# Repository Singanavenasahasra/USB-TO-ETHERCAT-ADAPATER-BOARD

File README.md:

# USB-to-EtherCAT Adapter Board

A compact hardware platform developed for interfacing USB systems with EtherCAT-based networks. The board was designed in KiCad with emphasis on clean circuit organization, efficient PCB routing, and practical hardware integration.

## Tools
- KiCad
- PCB Design & Layout

## Output
- Schematic
- PCB Layout
- Gerber Files
- Drill Files
- BOM

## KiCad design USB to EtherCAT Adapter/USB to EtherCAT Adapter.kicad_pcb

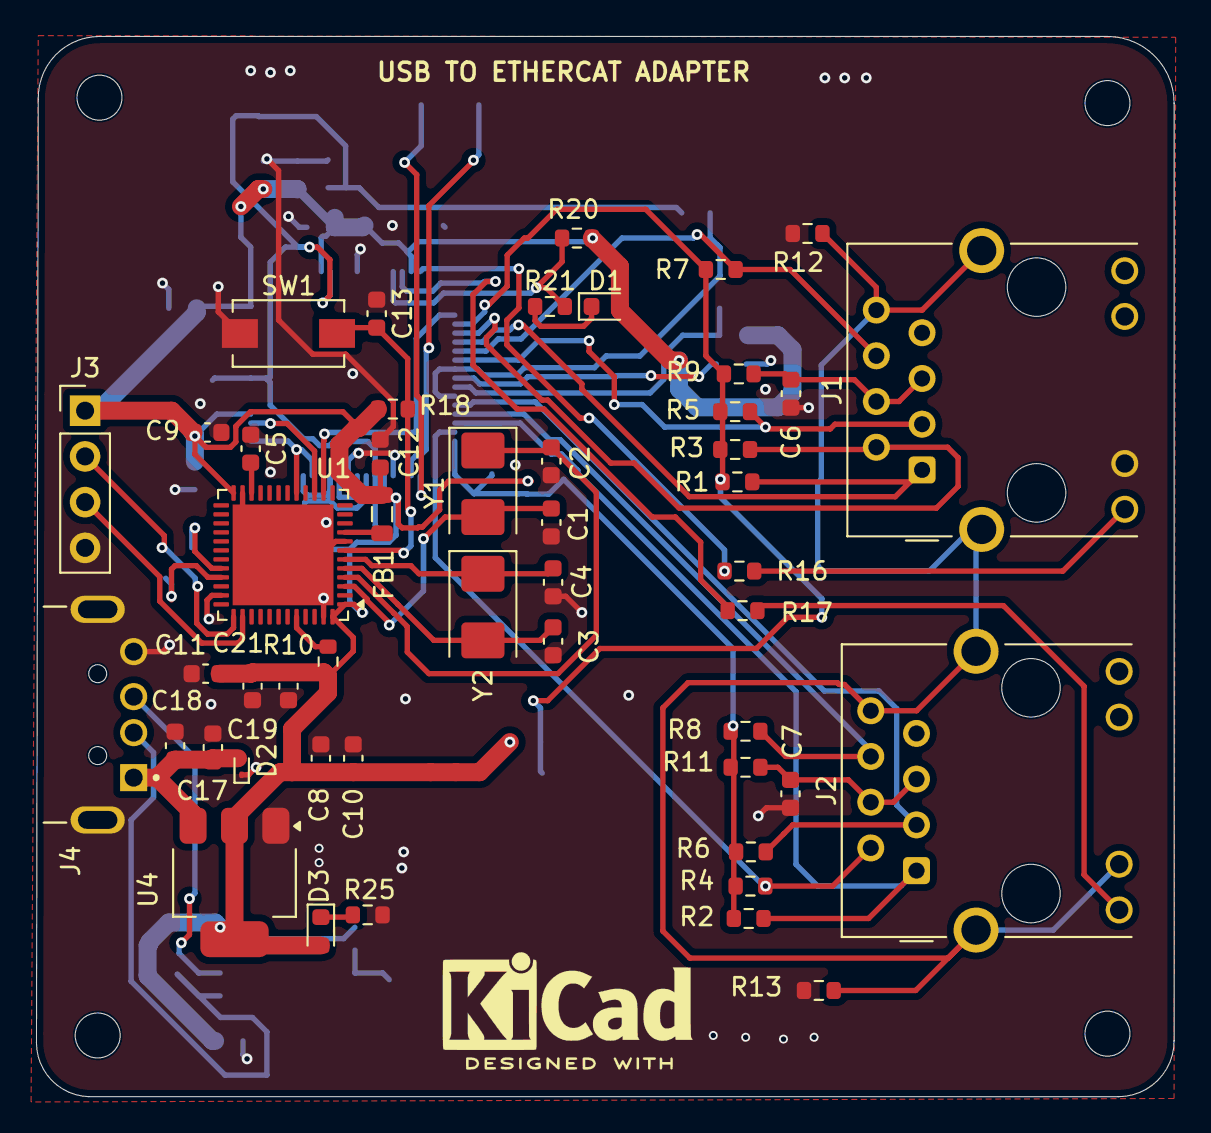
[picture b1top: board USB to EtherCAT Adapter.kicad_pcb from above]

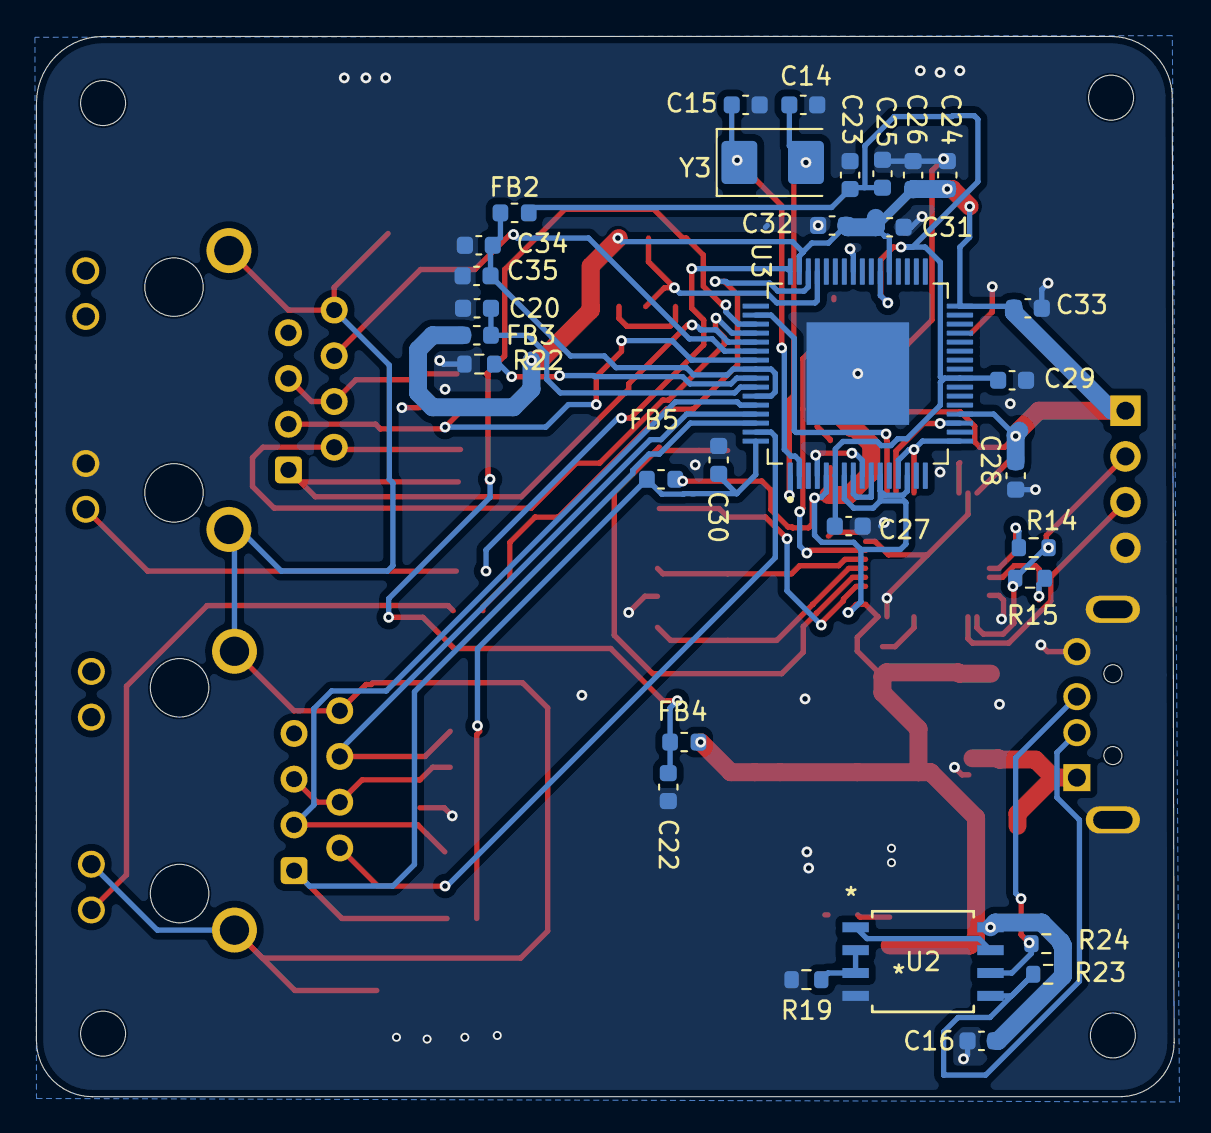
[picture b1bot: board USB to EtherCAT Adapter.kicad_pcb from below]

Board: 2 copper layers, 63.2 x 58.9 mm, 84 parts (31 on the bottom side), 49 nets.

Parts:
C1, C2, C3, C4, C14, C15: 12pf; C_0603_1608Metric
C5: 2.2uF; C_0603_1608Metric
C6, C7: 0.022uf; C_0603_1608Metric
C8, C9, C10, C11, C12, C13, C18, C19, C20, C22, C23, C24, C25, C26, C27, C28, C29, C30, C31, C32, C33, C34, C35: 0.1uf; C_0603_1608Metric
C16, C17, C21: 10uf; C_0603_1608Metric
D1, D3: LED; LED_0603_1608Metric
D2: ESD9B5.0ST5G; D_SOD-923
FB1: FerriteBead; L_0805_2012Metric
FB2: FerriteBead; L_0603_1608Metric
FB3, FB4, FB5: BLM18EG221SN1D; L_0603_1608Metric
H1, H2, H3, H4: MountingHole; MountingHole_2.5mm
J1, J2: RJ45_Hanrun_HR911105A_Horizontal
J3: Conn_01x04; PinHeader_1x04_P2.54mm_Vertical
J4: UP2-AH-1-TH; CUI_UP2-AH-1-TH
R1, R2, R3, R4, R5, R6, R7, R8: 49.9R; R_0603_1608Metric
R9, R11, R12, R13: 0R; R_0603_1608Metric
R10, R18: 10K; R_0603_1608Metric
R14, R15: 10R; R_0603_1608Metric
R16, R17, R20, R21, R25: 220R; R_0603_1608Metric
R19, R23, R24: 4.7K; R_0603_1608Metric
R22: 12.1K; R_0603_1608Metric
SW1: SW_Push; SW_SPST_EVQPE1
U1: STM32F411CEUx; QFN-48-1EP_7x7mm_P0.5mm_EP5.6x5.6mm
U2: 24FC512T-I/SM; SOIJ8-M_MC_MCH
U3: LAN9252_PT; QFP50P1200X1200X120-65N
U4: AMS1117-3.3; SOT-223-3_TabPin2
Y1, Y2, Y3: Crystal; Crystal_SMD_5032-2Pin_5.0x3.2mm

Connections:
+3V3: C8.1, C9.1, C10.1, C11.1, C12.1, C16.2, C19.2, C21.2, C24.2, C26.2, C28.2, C31.2, C32.2, C33.2, D1.2 (A), D3.2 (A), FB1.2, FB3.1, FB4.2, FB5.2, J3.1, R10.1, R18.1, R20.1, R23.2, R24.2, U1.1 (VBAT), U1.24 (VDD), U1.48 (VDD), U2.8 (VCC), U3.5 (VDD33), U3.7 (REG_EN), U3.11 (~RST), U3.14 (VDDIO), U3.20 (VDDIO), U3.32 (VDDIO), U3.37 (VDDIO), U3.47 (VDDIO), U4.2 (VO)
+5V: C17.2, C18.2, D2.2 (A2), J4.1 (VCC), U4.3 (VI)
GND: C1.1, C2.1, C3.1, C4.1, C5.1, C6.1, C7.1, C8.2, C9.2, C10.2, C11.2, C12.2, C13.1, C14.1, C15.1, C16.1, C17.1, C18.1, C19.1, C20.1, C21.1, C22.1, C23.1, C24.1, C25.1, C26.1, C27.1, C28.1, C29.1, C30.1, C31.1, C32.1, C33.1, C34.1, C35.1, D2.1 (A1), J1.10, J3.4, J4.4 (GND), J4.SH1 (SHIELD), J4.SH2 (SHIELD_1), R12.1, R13.1, R19.1, R22.1, R25.2, SW1.1, U1.8 (VSSA), U1.23 (VSS), U1.35 (VSS), U1.47 (VSS), U1.49 (VSS), U2.4 (VSS), U3.4 (OSCVSS), U3.9 (FXSDA/FXLOSA/~FXSDENA), U3.41 (TESTMODE), U3.65 (VSS), U4.1 (GND)
GNDA: J1.8, J1.SH, J2.8, J2.10, J2.SH, R12.2, R13.2
GPIO0: R16.2, U3.48 (LINKACTLED0/TDO/~CHIP_MODE0)
GPIO1: R17.2, U3.46 (LINKACTLED1/TDI/~CHIP_MODE1)
GPIO2: R20.2, R21.2, U3.45 (RUNLED/~E2PSIZE)
unnamed: D1.1 (K), R21.1
unnamed: D3.1 (K), R25.1
unnamed: J1.9, R16.1
unnamed: C6.2, J1.4 (TCT), J1.5 (RCT), R9.2
unnamed: J2.9, R17.1
unnamed: C7.2, J2.4 (TCT), J2.5 (RCT), R11.2
unnamed: R10.2, U1.44 (BOOT0)
unnamed: R14.1, U1.32 (PA11)
unnamed: R15.1, U1.33 (PA12)
unnamed: C1.2, U1.3 (PC14), Y1.2
unnamed: C2.2, U1.4 (PC15), Y1.1
unnamed: C3.2, U1.5 (PH0), Y2.2
unnamed: C4.2, U1.6 (PH1), Y2.1
unnamed: C5.2, U1.22 (VCAP1)
unnamed: FB1.1, U1.9 (VDDA)
unnamed: U2.1 (A0), U2.7 (WP)
unnamed: R19.2, U2.2 (A1), U2.3 (A2)
unnamed: U3.8 (~FXLOSEN), U3.10 (FXSDB/FXLOSB/~FXSDENB)
unnamed: C14.2, U3.1 (OSCI), Y3.2
unnamed: C15.2, U3.2 (OSCO), Y3.1
unnamed: R22.2, U3.57 (RBIAS)
unnamed: C20.2, FB3.2, U3.58 (VDD33BIAS)
RST: C13.2, R18.2, SW1.2, U1.7 (NRST)
RXNA: J1.6 (RD-), R7.2, U3.54 (RXNA)
RXNB: J2.6 (RD-), R8.2, U3.61 (RXNB)
RXPA: J1.3 (RD+), R5.2, U3.55 (RXPA)
RXPB: J2.3 (RD+), R6.2, U3.60 (RXPB)
SCK: U1.15 (PA5), U3.19 (D9/AD9/LATCH_IN/SCK)
SCS: U1.14 (PA4), U3.50 (D5/AD5/OUTVALID/SCS#)
SI: U1.17 (PA7), U3.13 (D1/AD1/EOF/SO/SIO1), U3.17 (D0/AD0/WD_STATE/SI/SIO0)
SWCLK: J3.3, U1.38 (PA15)
SWDIO: J3.2, R14.2, R15.2, U1.37 (PA14)
TXNA: J1.2 (TD-), R3.2, U3.52 (TXNA)
TXNB: J2.2 (TD-), R4.2, U3.63 (TXNB)
TXPA: J1.1 (TD+), R1.2, U3.53 (TXPA)
TXPB: J2.1 (TD+), R2.2, U3.62 (TXPB)
USB_DN: J4.2 (D-), R23.1, U2.5 (SDA)
USB_DP: J4.3 (D+), R24.1, U2.6 (SCL)
VDD12TX: C34.2, C35.2, FB2.1, U3.56 (VDD12TX1), U3.59 (VDD12TX2)
VDD33TXRX1: C22.2, FB4.1, R1.1, R3.1, R5.1, R7.1, R9.1, U3.51 (VDD33TXRX1)
VDD33TXRX2: C30.2, FB5.1, R2.1, R4.1, R6.1, R8.1, R11.1, U3.64 (VDD33TXRX2)
VDDCR: C23.2, C25.2, C27.2, C29.2, FB2.2, U3.6 (VDDCR), U3.24 (VDDCR), U3.38 (VDDCR)
